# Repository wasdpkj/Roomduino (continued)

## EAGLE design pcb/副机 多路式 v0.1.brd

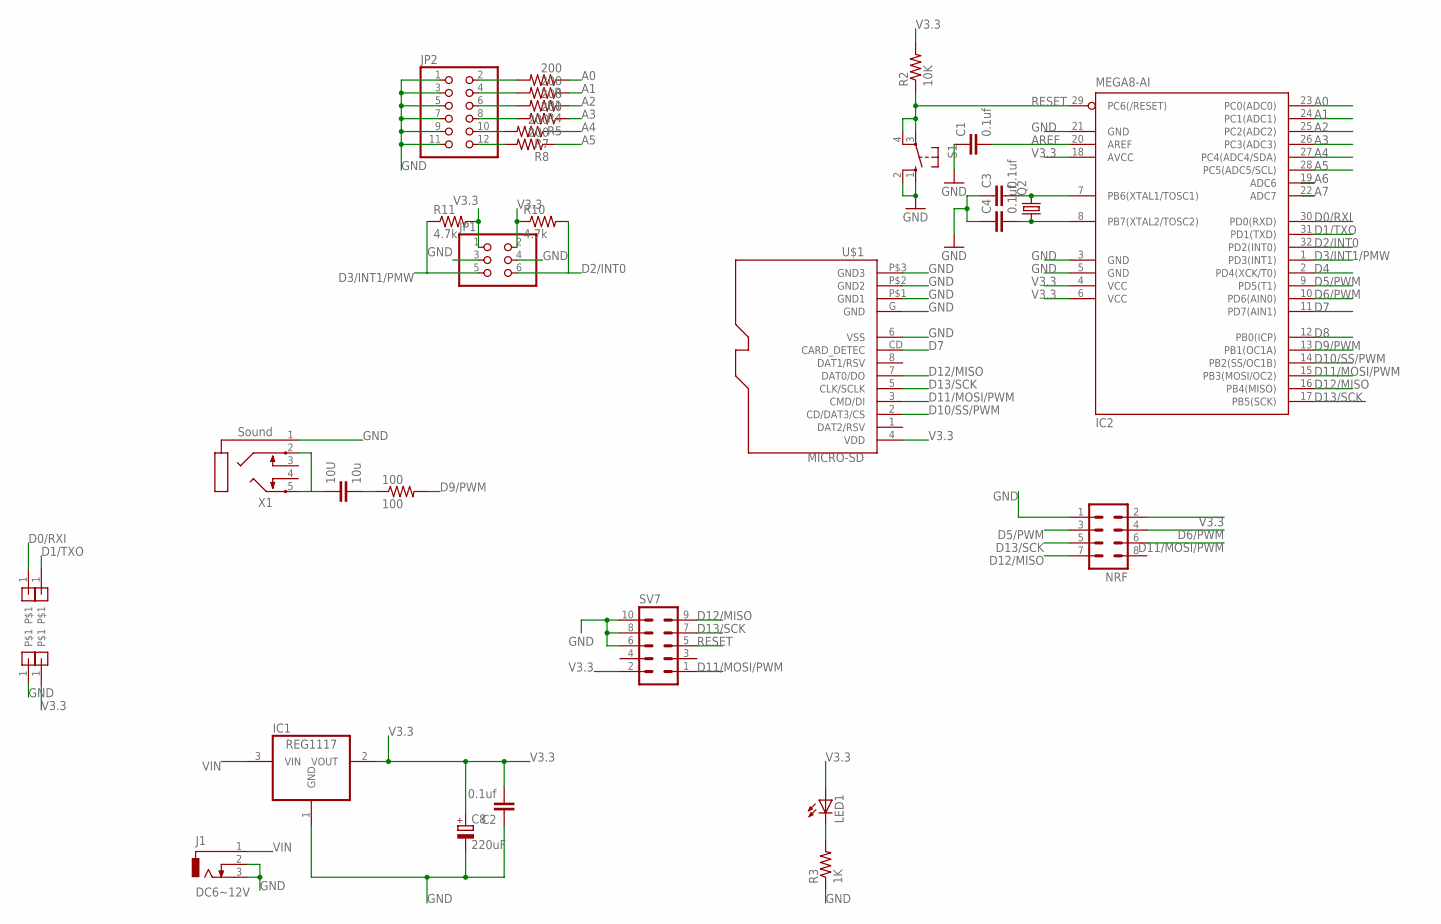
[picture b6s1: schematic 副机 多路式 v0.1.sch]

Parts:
10U: 10u; C050-024X044
100: 100; 0603-RES
C1, C2, C3, C4: 0.1uf; 0603-CAP
C8: 220uF; 153CLV-0605
IC1: REG1117; SOT223
IC2: MEGA8-AI; TQFP32-08
J1: DC6~12V; DCJ0202
JP1: PINHD-2X3; 2X03
JP2: PINHD-2X6; 2X06
LED1: LED0805; 0805-LED
NRF: MA04-2
Q2: CRYSTALHC49S; HC49/S
R, R1, R4, R5, R7, R8: 200; 0603-RES
R2: 10K; 0603-RES
R3: 1K; 0603-RES
R10, R11: 4.7k; 0603-RES
S1: 10-XX; B3F-10XX
SV7: MA05-2
U$1: MICRO-SD
U$4, U$5, U$6, U$7: PIN1
X1: Sound; STX3100

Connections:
A0: IC2.23 (PC0(ADC0)), R.1
A1: IC2.24 (PC1(ADC1)), R1.1
A2: IC2.25 (PC2(ADC2)), R4.1
A3: IC2.26 (PC3(ADC3)), R5.1
A4: IC2.27 (PC4(ADC4/SDA)), R7.1
A5: IC2.28 (PC5(ADC5/SCL)), R8.1
A6: IC2.19 (ADC6)
A7: IC2.22 (ADC7)
AREF: C1.2, IC2.20 (AREF)
D0/RXI: IC2.30 (PD0(RXD)), U$7.1
D1/TXO: IC2.31 (PD1(TXD)), U$6.1
D2/INT0: IC2.32 (PD2(INT0)), JP1.6, R10.2
D3/INT1/PMW: IC2.1 (PD3(INT1)), JP1.5, R11.1
D4: IC2.2 (PD4(XCK/T0))
D5/PWM: IC2.9 (PD5(T1)), NRF.3
D6/PWM: IC2.10 (PD6(AIN0)), NRF.4
D7: IC2.11 (PD7(AIN1)), U$1.CD (CARD_DETEC)
D8: IC2.12 (PB0(ICP))
D9/PWM: 100.2, IC2.13 (PB1(OC1A))
D10/SS/PWM: IC2.14 (PB2(SS/OC1B)), U$1.2 (CD/DAT3/CS)
D11/MOSI/PWM: IC2.15 (PB3(MOSI/OC2)), NRF.6, SV7.1, U$1.3 (CMD/DI)
D12/MISO: IC2.16 (PB4(MISO)), NRF.7, SV7.9, U$1.7 (DAT0/DO)
D13/SCK: IC2.17 (PB5(SCK)), NRF.5, SV7.7, U$1.5 (CLK/SCLK)
GND: C1.1, C2.1, C3.1, C4.1, C8.-, IC1.1 (GND), IC2.3 (GND), IC2.5 (GND), IC2.21 (GND), J1.2, J1.3, JP1.3, JP1.4, JP2.1, JP2.3, JP2.5, JP2.7, JP2.9, JP2.11, NRF.1, R3.1, S1.1 (S), S1.2 (S1), SV7.6, SV7.8, SV7.10, U$1.6 (VSS), U$1.G (GND), U$1.P$1 (GND1), U$1.P$2 (GND2), U$1.P$3 (GND3), U$4.1, X1.1
unnamed: JP2.2, R.2
unnamed: JP2.12, R8.2
unnamed: JP2.4, R1.2
unnamed: LED1.C, R3.2
unnamed: JP2.6, R4.2
unnamed: JP2.8, R5.2
unnamed: JP2.10, R7.2
unnamed: 10U.2, 100.1
PB6: C3.2, IC2.7 (PB6(XTAL1/TOSC1)), Q2.2
PB7: C4.2, IC2.8 (PB7(XTAL2/TOSC2)), Q2.1
RESET: IC2.29 (PC6(/RESET)), R2.1, S1.3, S1.4 (P1), SV7.5
V3.3: C2.2, C8.+, IC1.2 (VOUT), IC2.4 (VCC), IC2.6 (VCC), IC2.18 (AVCC), JP1.1, JP1.2, LED1.A, NRF.2, R2.2, R10.1, R11.2, SV7.2, U$1.4 (VDD), U$5.1
VIN: IC1.3 (VIN), J1.1
~~: 10U.1, X1.2, X1.5

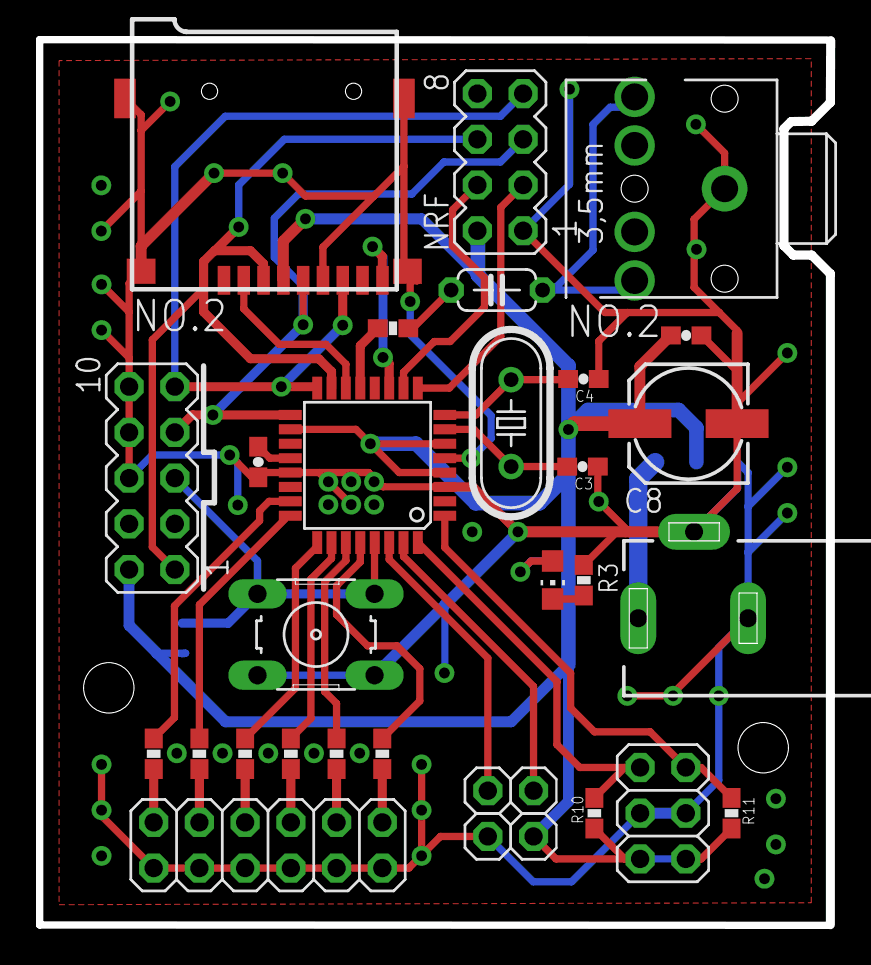
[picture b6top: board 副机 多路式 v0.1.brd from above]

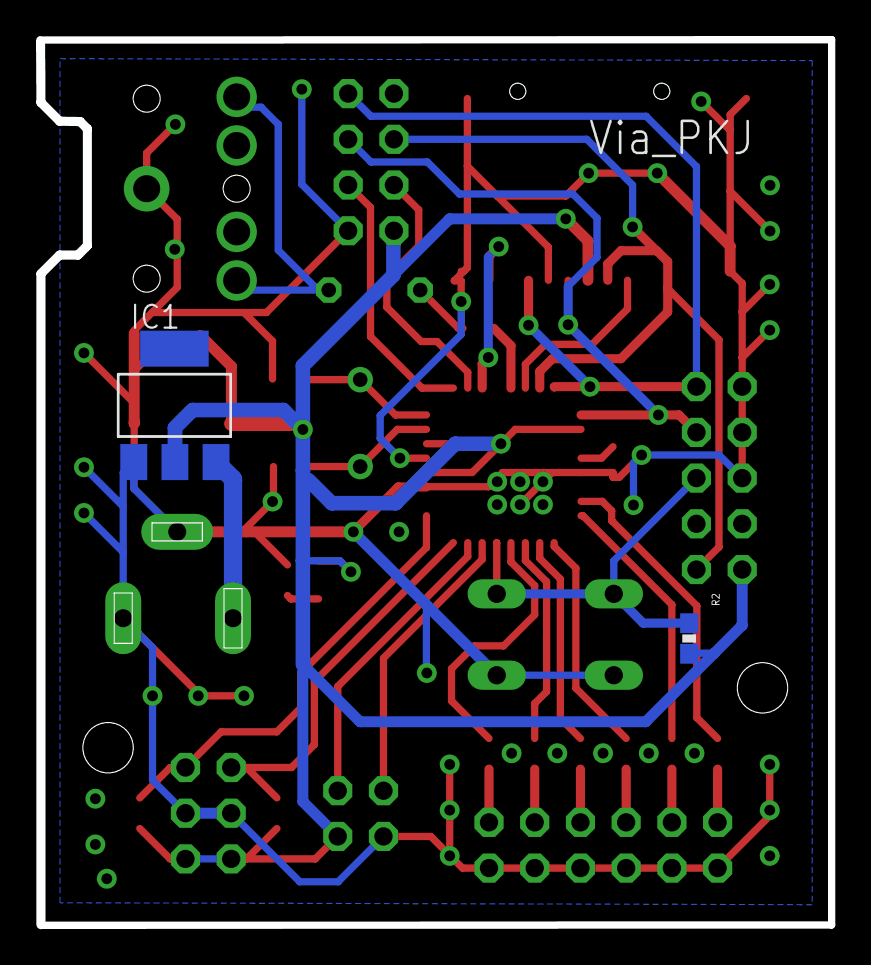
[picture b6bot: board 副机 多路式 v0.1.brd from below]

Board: 2 copper layers, 43.9 x 49.2 mm, 33 parts (2 on the bottom side), 34 nets.

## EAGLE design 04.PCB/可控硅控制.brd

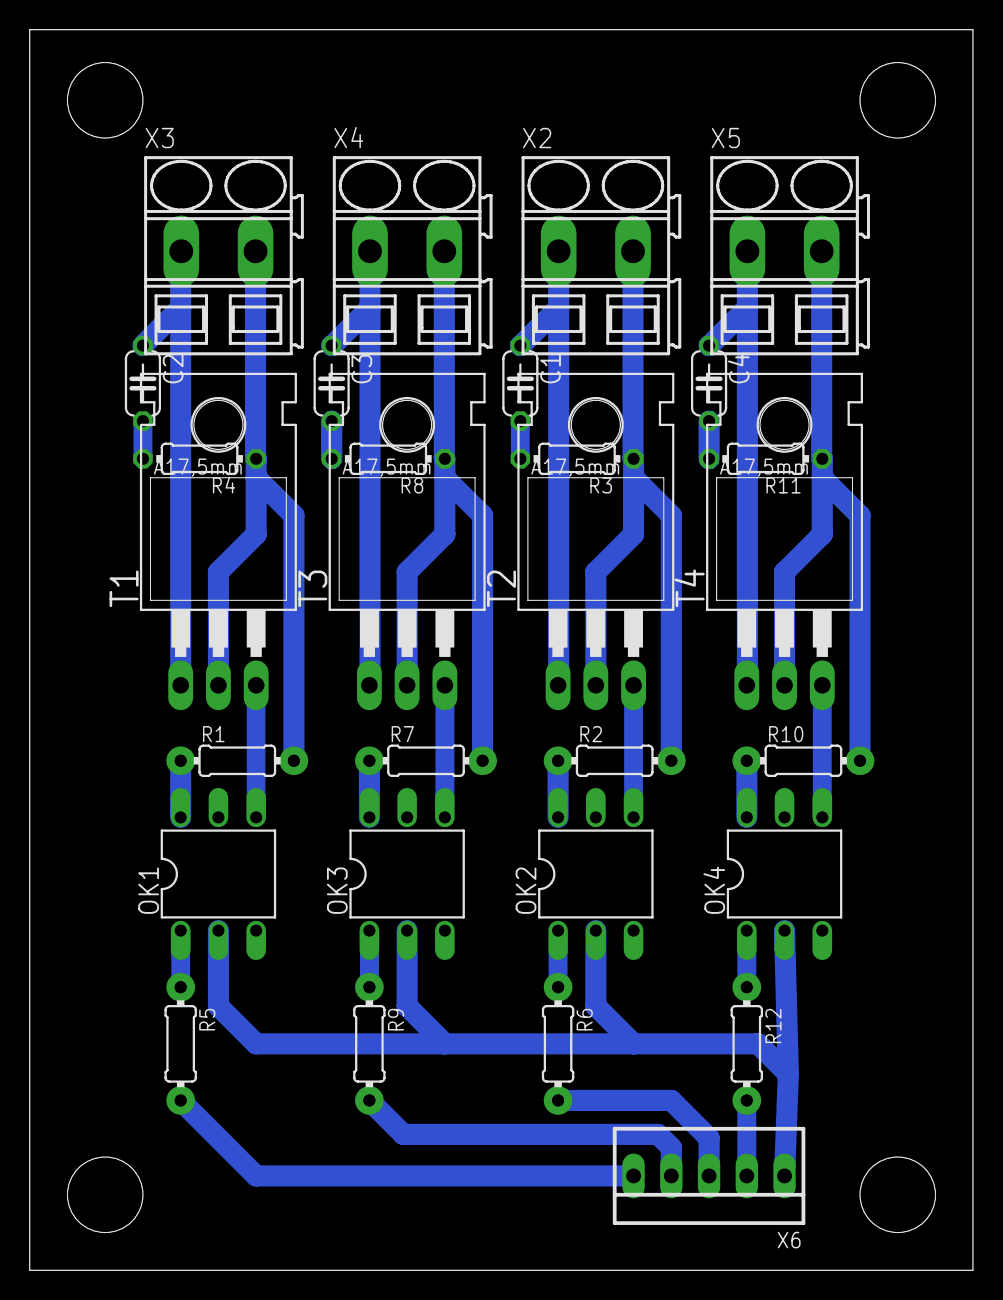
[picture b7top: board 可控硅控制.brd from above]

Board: 2 copper layers, 63.5 x 83.5 mm, 29 parts (0 on the bottom side), 29 nets.

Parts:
C1, C2, C3, C4: 0.01u; C050-024X044
OK1, OK2, OK3, OK4: MOC3041M; DIL06
R1, R2, R7, R10: 2K/330; 0204/7
R3, R4, R8, R11: 100; 0204/7
R5, R6, R9, R12: 47; 0204/7
T1, T2, T3, T4: BT136; TO220AB
X2, X3, X4, X5: SMKDSP_1,5/2
X6: 22-23-2051

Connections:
11: OK1.1, R5.1
22: OK3.1, R9.1
33: OK4.1, R12.1
44: OK2.1, R6.1
A1: R1.2, R4.1, T1.2, X3.2
A2: C2.1, T1.1, X3.1
B1: R7.2, R8.1, T3.2, X4.2
B2: C3.1, T3.1, X4.1
C1: R2.2, R3.1, T2.2, X2.2
C2: C1.1, T2.1, X2.1
D1: R10.2, R11.1, T4.2, X5.2
D2: C4.1, T4.1, X5.1
GND: OK1.2, OK2.2, OK3.2, OK4.2, X6.1
unnamed: OK1.6, R1.1
unnamed: OK1.4, T1.3
unnamed: C2.2, R4.2
unnamed: OK2.6, R2.1
unnamed: OK2.4, T2.3
unnamed: C1.2, R3.2
unnamed: OK3.6, R7.1
unnamed: OK3.4, T3.3
unnamed: C3.2, R8.2
unnamed: OK4.6, R10.1
unnamed: OK4.4, T4.3
unnamed: C4.2, R11.2
P1: R5.2, X6.5
P2: R9.2, X6.4
P3: R6.2, X6.3
P4: R12.2, X6.2

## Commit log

2013-06-27 Roomduino
2013-06-27 V0.4
2013-06-27 V0.4主机程序无论用5110还是oled，写在一个程序了，在define中选择
    主机程序无论用5110还是oled，写在一个程序了，在define中选择
2013-06-29 V0.5 修正了菜单显示bug
    V0.5 修正了菜单显示bug
2013-06-29 V0.5
    V0.5 修正了显示问题
2013-06-30 V0.6更新了温湿度查错
    V0.6更新了温湿度查错
2013-06-30 增加dht11的库
    增加dht11的库
2013-06-30 更新了温湿度查错
    更新了温湿度查错
2013-07-10 更新了Microduino面包版PCB
    更新了Microduino面包版PCB
2013-07-13 解决了millis()溢出问题
    解决了millis()溢出问题
2013-07-17 优化了变量
    优化了变量
2013-08-16 更新文件夹名称
2013-09-02 更新了几个新pcb
    更新了几个新pcb
2013-11-09 程序引脚请自己定义
2013-11-09 单片机改用5v供电，ISP下载口也是5v电压
